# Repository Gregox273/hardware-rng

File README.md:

# hardware-rng
Random number generation using diode avalanche noise (for Master's project)

Based on the 'Hororan' circuit by Professor Paul Horowitz:  
*Page 984, Art of Electronics Third Edition,*  
*Paul Horowitz, Winfield Hill 2015*  
*ISBN 978-0-521-80926-9*

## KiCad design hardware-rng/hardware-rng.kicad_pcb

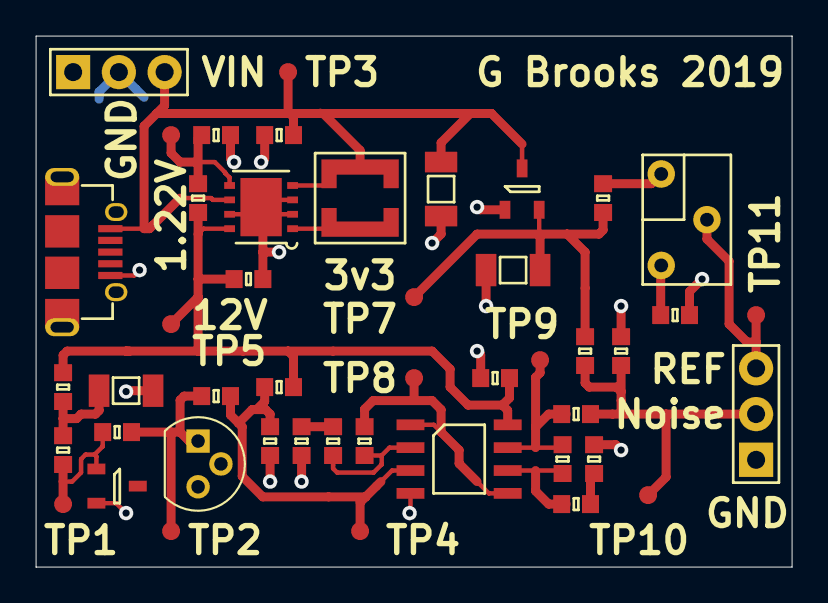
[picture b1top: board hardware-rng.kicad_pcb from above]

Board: 2 copper layers, 42.0 x 29.5 mm, 46 parts (0 on the bottom side), 20 nets.

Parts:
C1, C3, C7: 1.5uF; 1206
C2: 4.7nF; 0603
C4, C8: 10uF; 0603
C5, C6: 33nF; 0603
C9: 100nF; 0603
C10: 3.3nF; 0603
D1: LM4040-10V; SOT-23
IC1: MCP1700; SOT-23
J1: MICROUSB; MICROUSB_MOLEX_47589-0001
J2, J3: CONN_01x03; SIL-254P-03
L1: 4.7uH; WURTH_IND_3.8_3.8_1.65
Q1: 2N4401; TO-92
R1, R2, R4, R5, R12, R13: 1k; 0603
R3: 100k; 0603
R6, R11, R14, R16: 2.49k; 0603
R7, R10: 249; 0603
R8: 180k; 0603
R9: 20k; 0603
R15: 1k potentiometer; 3266W_trimpot
TP1, TP2, TP3, TP4, TP5, TP6, TP7, TP8, TP9, TP10, TP11: TESTPAD
U1: ST8R00; DFN-8-ST
U2: LT1215CS8#PBF; SOIC-8

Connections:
3v3: C7.1, IC1.2, R12.1, R14.2, TP7.1
12v: C8.2, C9.1, R1.1, R4.1, R8.1, TP5.1, U1.8, U2.8
GND: C1.2, C3.2, C4.1, C5.2, C6.2, C7.2, C8.1, C9.2, D1.2, IC1.1, J1.5, J2.2, J3.1, Q1.1, R5.2, R9.2, R13.2, R16.1, U1.2, U1.3, U1.7, U1.EP, U2.4
unnamed: C1.1, R1.2, R2.1
unnamed: C2.1, Q1.2, R3.1, TP2.1
unnamed: C2.2, R4.2, R5.1, TP4.1, U2.3
unnamed: C5.1, R7.2
unnamed: C6.1, R10.2
unnamed: C10.1, R11.1, TP9.1, U2.7
unnamed: C10.2, J3.2, R12.2, R13.1, TP10.1
unnamed: D1.1, R2.2, R3.2, TP1.1
unnamed: J3.3, R15.2, TP11.1
unnamed: L1.2, U1.1
unnamed: R6.1, R7.1, U2.2
unnamed: R6.2, TP8.1, U2.1, U2.5
unnamed: R8.2, R9.1, TP6.1, U1.5
unnamed: R10.1, R11.2, U2.6
unnamed: R14.1, R15.1
unnamed: R15.3, R16.2
VCC: C3.1, C4.2, IC1.3, J1.1, J2.3, L1.1, TP3.1, U1.4, U1.6

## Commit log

2019-03-09 Begin schematic
2019-03-09 Finish first schematic iteration
2019-03-09 Remove .bak
2019-03-09 Begin PCB
2019-03-09 More work on PCB
2019-03-09 Remove digital potentiometer from project
2019-03-09 Finish first revision of PCB
2019-03-09 Add gerbers
2019-03-09 Add LTSpice simulation of potentiometer bias circuit
2019-03-14 Rearrange schematic
2019-05-21 Replace the word 'zener', since the circuit uses avalanche, rather than zener breakdown
2019-05-21 Remove leftover comment from schematic
